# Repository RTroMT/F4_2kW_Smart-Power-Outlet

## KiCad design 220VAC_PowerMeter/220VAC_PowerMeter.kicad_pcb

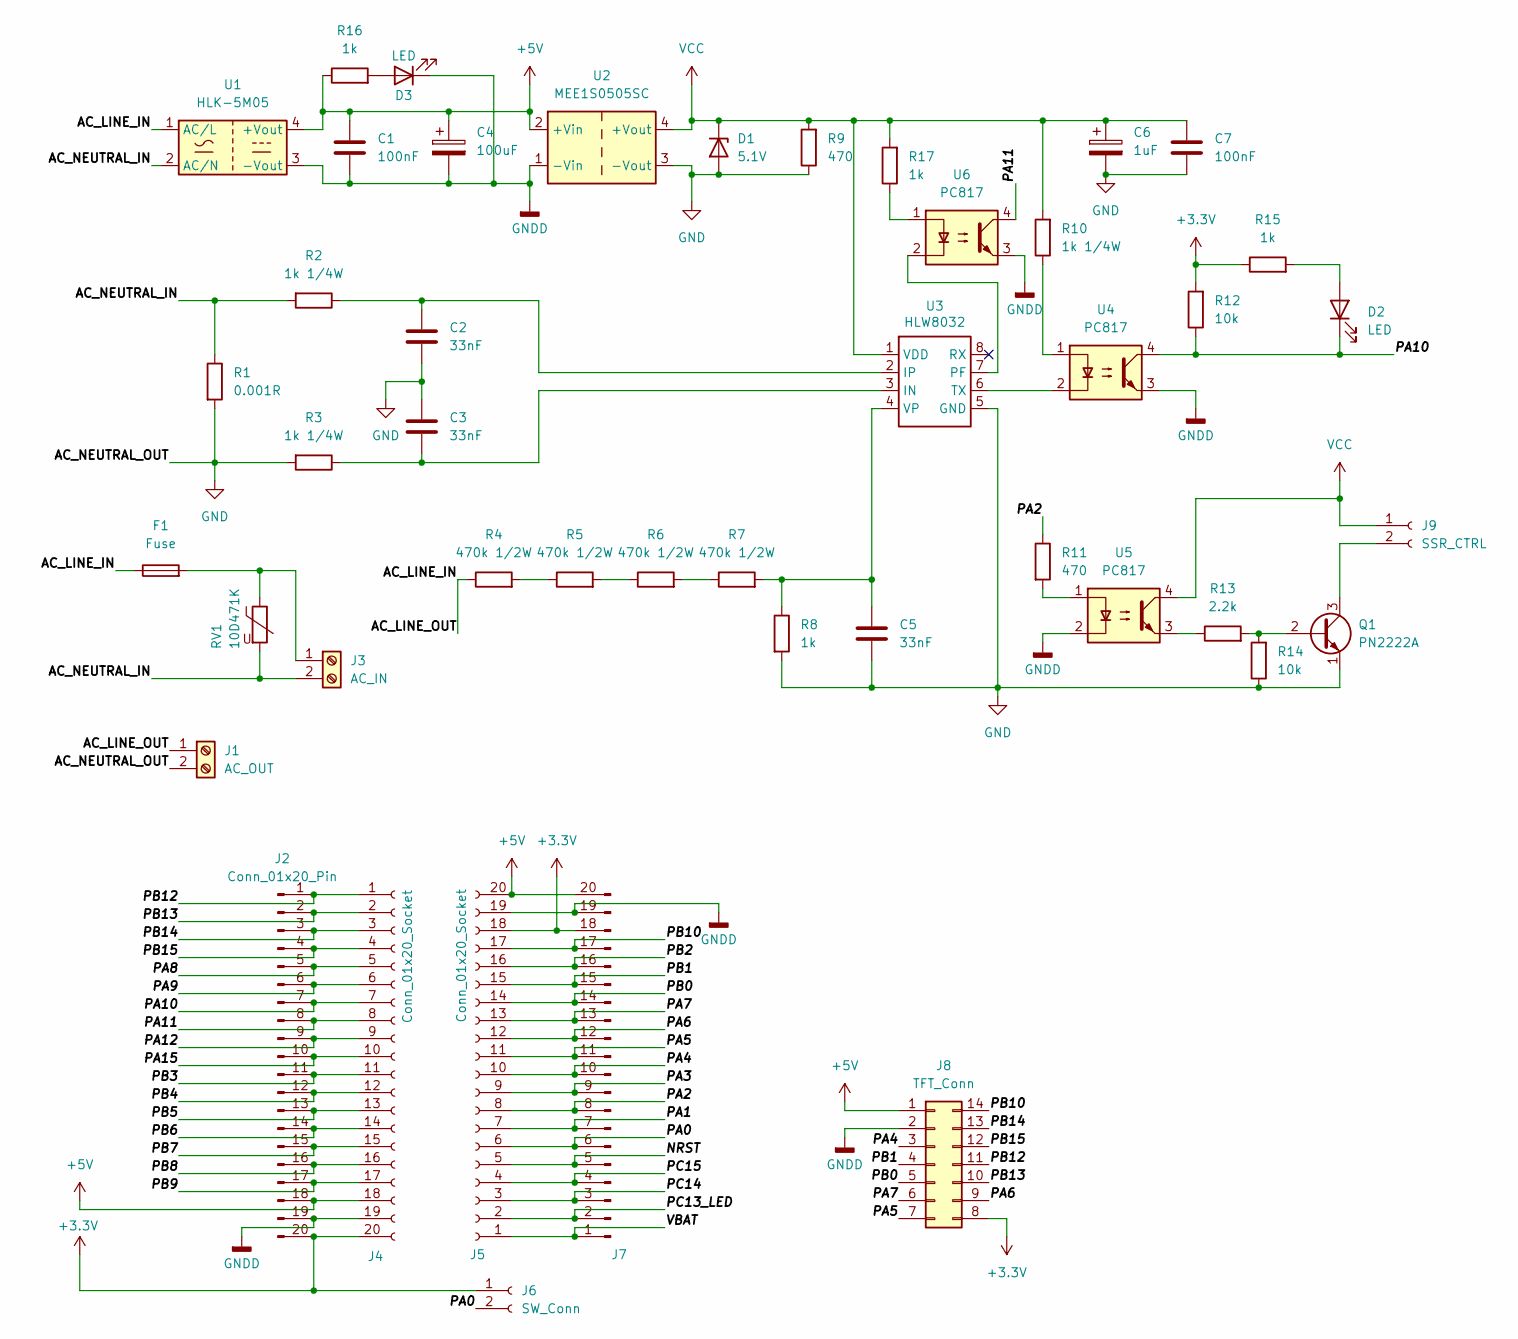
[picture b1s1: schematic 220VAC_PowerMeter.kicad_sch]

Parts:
C1, C7: 100nF; C_0805_2012Metric_Pad1.18x1.45mm_HandSolder
C2, C3: 33nF; C_Rect_L11.0mm_W5.1mm_P10.00mm_MKT
C4: 100uF; CP_Radial_D5.0mm_P2.50mm
C5: 33nF; C_0805_2012Metric_Pad1.18x1.45mm_HandSolder
C6: 1uF; CP_Radial_D5.0mm_P2.00mm
D1: 5.1V; D_DO-41_SOD81_P3.81mm_Vertical_AnodeUp
D2, D3: LED; LED_D3.0mm
F1: Fuse; Fuseholder_Clip-5x20mm_Eaton_1A5601-01_Inline_P20.80x6.76mm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
J1: AC_OUT; TerminalBlock_Ningbo-Kagnex_HB9500_1x02_P9.5mm
J2: Conn_01x20_Pin; PinHeader_1x20_P2.54mm_Vertical
J3: AC_IN; TerminalBlock_Ningbo-Kagnex_HB9500_1x02_P9.5mm
J4, J5: Conn_01x20_Socket; PinSocket_1x20_P2.54mm_Vertical
J6: SW_Conn; JST_XH_B2B-XH-A_1x02_P2.50mm_Vertical
J7: PinHeader_1x20_P2.54mm_Vertical
J8: TFT_Conn; IDC-Header_2x07_P2.54mm_Vertical
J9: SSR_CTRL; JST_XH_B2B-XH-A_1x02_P2.50mm_Vertical
Q1: PN2222A; TO-92_Inline
R1: 0.001R; R_Axial_DIN0207_L6.3mm_D2.5mm_P10.16mm_Horizontal
R2, R3, R10: 1k 1/4W; R_Axial_DIN0207_L6.3mm_D2.5mm_P7.62mm_Horizontal
R4, R5, R6, R7: 470k 1/2W; R_Axial_DIN0207_L6.3mm_D2.5mm_P10.16mm_Horizontal
R8: 1k; R_Axial_DIN0207_L6.3mm_D2.5mm_P10.16mm_Horizontal
R9, R11: 470; R_Axial_DIN0207_L6.3mm_D2.5mm_P7.62mm_Horizontal
R12, R14: 10k; R_Axial_DIN0207_L6.3mm_D2.5mm_P7.62mm_Horizontal
R13: 2.2k; R_Axial_DIN0207_L6.3mm_D2.5mm_P7.62mm_Horizontal
R15, R16, R17: 1k; R_Axial_DIN0207_L6.3mm_D2.5mm_P7.62mm_Horizontal
RV1: 10D471K; RV_Disc_D12mm_W5.4mm_P7.5mm
U1: HLK-5M05; Converter_ACDC_Hi-Link_HLK-5Mxx
U2: MEE1S0505SC; Converter_DCDC_Murata_MEE1SxxxxSC_THT
U3: HLW8032; SOIC-8_3.9x4.9mm_P1.27mm
U4, U5, U6: PC817; DIP-4_W7.62mm_LongPads

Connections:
+3.3V: J2.20, J4.20, J5.18, J6.1, J7.18, J8.8, R12.2, R15.1
+5V: C1.1, C4.1, J2.18, J4.18, J5.20, J7.20, J8.1, R16.1, U1.4 (+Vout), U2.2 (+Vin); also elsewhere on the board
/AC_LINE_IN: F1.1, J1.1, R4.1, U1.1 (AC/L)
/AC_NEUTRAL_IN: J3.2, R1.1, R2.2, RV1.2, U1.2 (AC/N)
/NRST: J5.5, J7.5
/PA0: J5.6, J6.2, J7.6
/PA1: J5.7, J7.7
/PA2: J5.8, J7.8, R11.1
/PA3: J5.9, J7.9
/PA4: J5.10, J7.10, J8.3
/PA5: J5.11, J7.11, J8.7
/PA6: J5.12, J7.12, J8.9
/PA7: J5.13, J7.13, J8.6
/PA8: J2.5, J4.5
/PA9: J2.6, J4.6
/PA10: D2.1 (K), J2.7, J4.7, R12.1, U4.4
/PA11: J2.8, J4.8, U6.4
/PA12: J2.9, J4.9
/PA15: J2.10, J4.10
/PB0: J5.14, J7.14, J8.5
/PB1: J5.15, J7.15, J8.4
/PB2: J5.16, J7.16
/PB3: J2.11, J4.11
/PB4: J2.12, J4.12
/PB5: J2.13, J4.13
/PB6: J2.14, J4.14
/PB7: J2.15, J4.15
/PB8: J2.16, J4.16
/PB9: J2.17, J4.17
/PB10: J5.17, J7.17, J8.14
/PB12: J2.1, J4.1, J8.11
/PB13: J2.2, J4.2, J8.10
/PB14: J2.3, J4.3, J8.13
/PB15: J2.4, J4.4, J8.12
/PC13_LED: J5.2, J7.2
/PC14: J5.3, J7.3
/PC15: J5.4, J7.4
/VBAT: J5.1, J7.1
GND: C2.2, C3.1, C5.2, C6.2, C7.2, D1.2 (A), J1.2, Q1.1 (E), R1.2, R3.2, R8.2, R9.1, R14.1, U2.3 (-Vout), U3.5 (GND)
GNDD: C1.2, C4.2, D3.1 (K), J2.19, J4.19, J5.19, J7.19, J8.2, U1.3 (-Vout), U2.1 (-Vin), U4.3, U5.2, U6.3; also elsewhere on the board
unnamed: D2.2 (A), R15.2
unnamed: D3.2 (A), R16.2
unnamed: F1.2, J3.1, RV1.1
unnamed: J9.2, Q1.3 (C)
unnamed: Q1.2 (B), R13.2, R14.2
unnamed: R4.2, R5.1
unnamed: R5.2, R6.1
unnamed: R6.2, R7.1
unnamed: R10.1, U4.1
unnamed: R11.2, U5.1
unnamed: R13.1, U5.3
unnamed: R17.1, U6.1
unnamed: C3.2, R3.1, U3.3 (IN)
unnamed: C2.1, R2.1, U3.2 (IP)
unnamed: U3.7 (PF), U6.2
unnamed: U3.6 (TX), U4.2
unnamed: C5.1, R7.2, R8.1, U3.4 (VP)
VCC: C6.1, C7.1, D1.1 (K), J9.1, R9.2, R10.2, R17.2, U2.4 (+Vout), U3.1 (VDD), U5.4

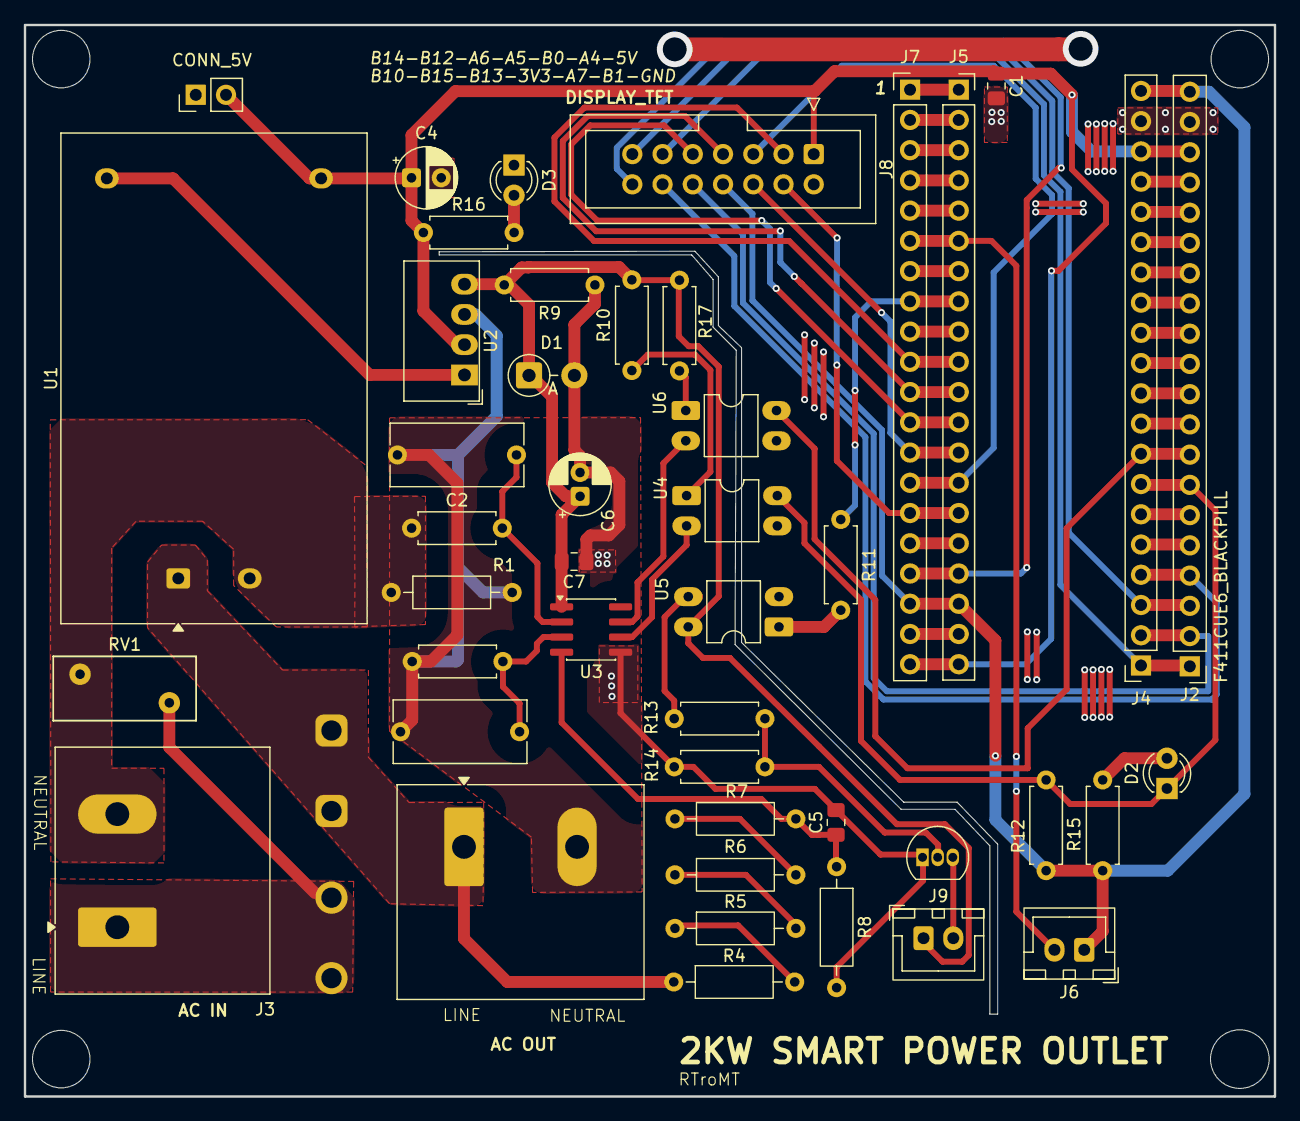
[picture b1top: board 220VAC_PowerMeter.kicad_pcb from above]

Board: 2 copper layers, 105.0 x 90.0 mm, 46 parts (1 on the bottom side), 58 nets.

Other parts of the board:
CONN_5V: PinHeader_1x02_P2.54mm_Vertical

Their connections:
+5V: CONN_5V.2; also elsewhere on the board
GNDD: CONN_5V.1; also elsewhere on the board

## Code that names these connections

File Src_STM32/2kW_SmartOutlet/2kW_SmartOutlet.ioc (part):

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Mcu.Name=STM32F401C(B-C)Ux
Mcu.Package=UFQFPN48
Mcu.UserName=STM32F401CCUx
PA0-WKUP.GPIOParameters=GPIO_PuPd,GPIO_Label
PA0-WKUP.GPIO_Label=SW_MAIN
PA0-WKUP.GPIO_PuPd=GPIO_PULLDOWN
PA0-WKUP.Signal=GPIO_Input
PA10.Mode=Asynchronous
PA10.Signal=USART1_RX
PA11.Mode=Asynchronous
PA11.Signal=USART6_TX
PA12.Mode=Asynchronous
PA12.Signal=USART6_RX
PA13.Mode=Serial_Wire
PA13.Signal=SYS_JTMS-SWDIO
PA14.Mode=Serial_Wire
PA14.Signal=SYS_JTCK-SWCLK
PA2.GPIOParameters=GPIO_Speed,GPIO_PuPd,GPIO_Label
PA2.GPIO_Label=SSR_CTRL
PA2.GPIO_PuPd=GPIO_PULLDOWN
PA2.GPIO_Speed=GPIO_SPEED_FREQ_VERY_HIGH
PA2.Signal=GPIO_Output
PA4.GPIOParameters=GPIO_Speed,PinState,GPIO_Label
PA4.GPIO_Label=TFT_CS
PA4.GPIO_Speed=GPIO_SPEED_FREQ_VERY_HIGH
PA4.PinState=GPIO_PIN_RESET
PA4.Signal=GPIO_Output
PA5.Mode=Full_Duplex_Master
PA5.Signal=SPI1_SCK
PA6.Mode=Full_Duplex_Master
PA6.Signal=SPI1_MISO
PA7.Mode=Full_Duplex_Master
PA7.Signal=SPI1_MOSI
PA9.Mode=Asynchronous
PA9.Signal=USART1_TX
PB0.GPIOParameters=GPIO_Speed,GPIO_Label
PB0.GPIO_Label=TFT_A0
PB0.GPIO_Speed=GPIO_SPEED_FREQ_VERY_HIGH
PB0.Signal=GPIO_Output
PB1.GPIOParameters=GPIO_Speed,GPIO_Label
PB1.GPIO_Label=TFT_RESET
PB1.GPIO_Speed=GPIO_SPEED_FREQ_VERY_HIGH
PB1.Signal=GPIO_Output
PB10.GPIOParameters=GPIO_PuPd,GPIO_Label
PB10.GPIO_Label=TOUCH_IRQ
PB10.GPIO_PuPd=GPIO_PULLUP
PB10.Signal=GPIO_Input
PB12.GPIOParameters=GPIO_Speed,GPIO_Label
PB12.GPIO_Label=TOUCH_CS
PB12.GPIO_Speed=GPIO_SPEED_FREQ_VERY_HIGH
PB12.Signal=GPIO_Output
PB13.GPIOParameters=GPIO_Speed,GPIO_Label
PB13.GPIO_Label=TOUCH_CLK
PB13.GPIO_Speed=GPIO_SPEED_FREQ_VERY_HIGH
PB13.Signal=GPIO_Output
PB14.GPIOParameters=GPIO_PuPd,GPIO_Label
PB14.GPIO_Label=TOUCH_DO
PB14.GPIO_PuPd=GPIO_PULLUP
PB14.Signal=GPIO_Input
PB15.GPIOParameters=GPIO_Speed,GPIO_Label
PB15.GPIO_Label=TOUCH_DIN
PB15.GPIO_Speed=GPIO_SPEED_FREQ_VERY_HIGH
PB15.Signal=GPIO_Output
PC13-ANTI_TAMP.GPIOParameters=GPIO_Label
PC13-ANTI_TAMP.GPIO_Label=LED_BUILTIN
PC13-ANTI_TAMP.Signal=GPIO_Output
PH0\ -\ OSC_IN.Mode=HSE-External-Oscillator
PH0\ -\ OSC_IN.Signal=RCC_OSC_IN
PH1\ -\ OSC_OUT.Mode=HSE-External-Oscillator
PH1\ -\ OSC_OUT.Signal=RCC_OSC_OUT
RCC.HSE_VALUE=25000000
RCC.SYSCLKFreq_VALUE=84000000
RCC.SYSCLKSource=RCC_SYSCLKSOURCE_PLLCLK
board=custom
